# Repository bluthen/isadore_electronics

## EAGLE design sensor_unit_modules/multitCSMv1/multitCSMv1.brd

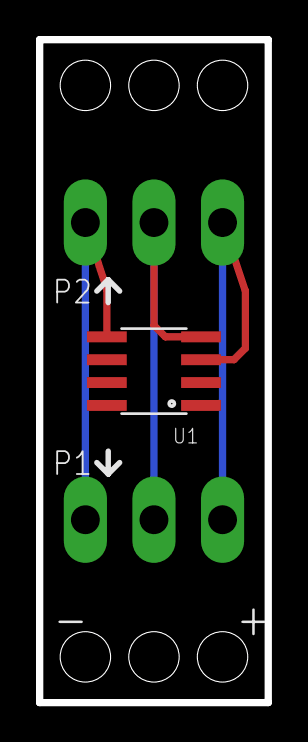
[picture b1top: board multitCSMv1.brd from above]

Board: 2 copper layers, 12.7 x 36.8 mm, 3 parts (0 on the bottom side), 3 nets.

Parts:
E$3, E$4: 1X03_BIGPAD
U1: SO08

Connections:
S$1: E$3.P$2, E$4.P$2, U1.5
S$2: E$3.P$1, E$4.P$1, U1.4
S$3: E$3.P$3, E$4.P$3, U1.3

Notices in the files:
parts and their libraries:
SparkFun-DigitalIC: Licensing: CC v3.0 Share-Alike You are welcome to use this library for commercial purposes.
